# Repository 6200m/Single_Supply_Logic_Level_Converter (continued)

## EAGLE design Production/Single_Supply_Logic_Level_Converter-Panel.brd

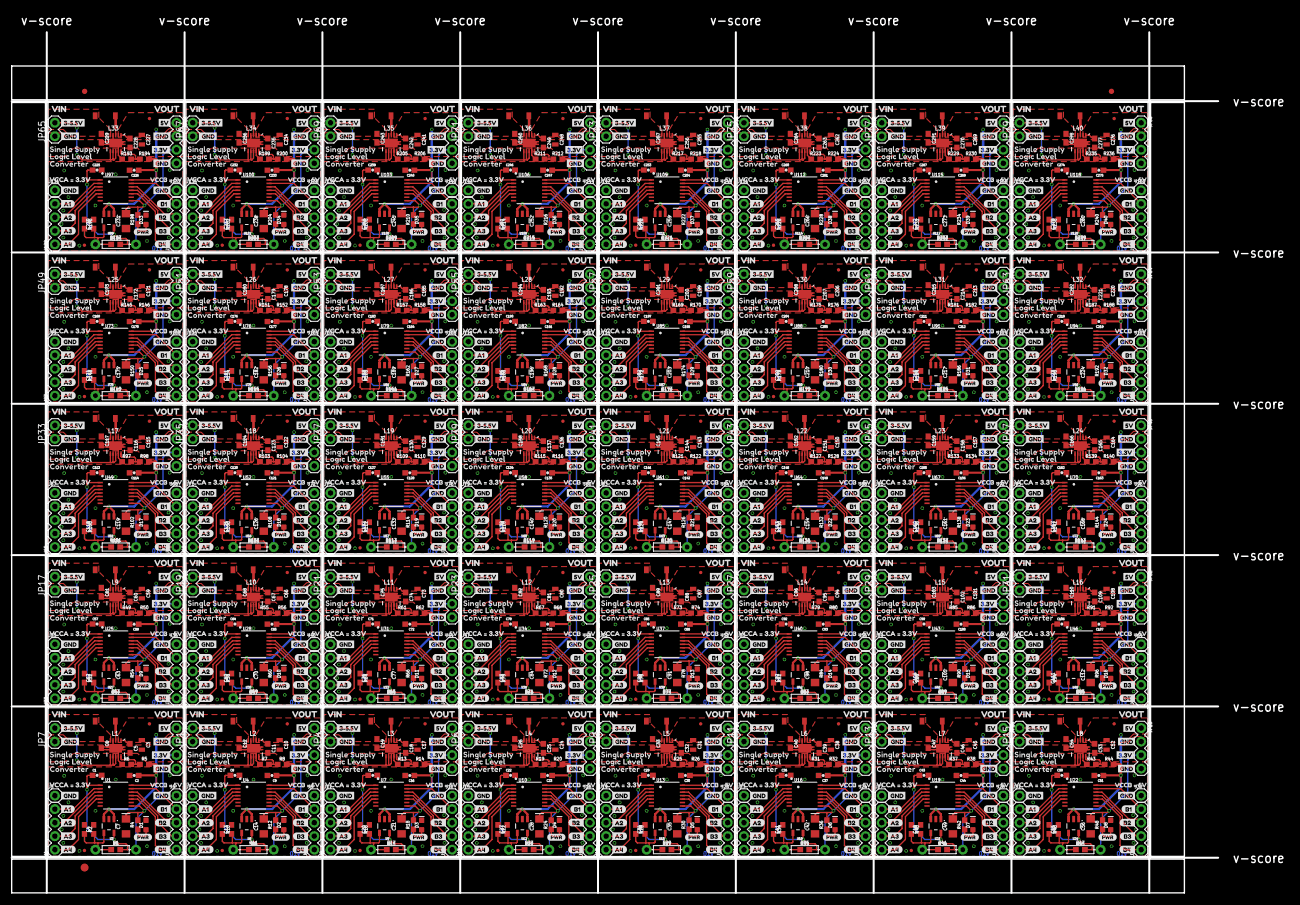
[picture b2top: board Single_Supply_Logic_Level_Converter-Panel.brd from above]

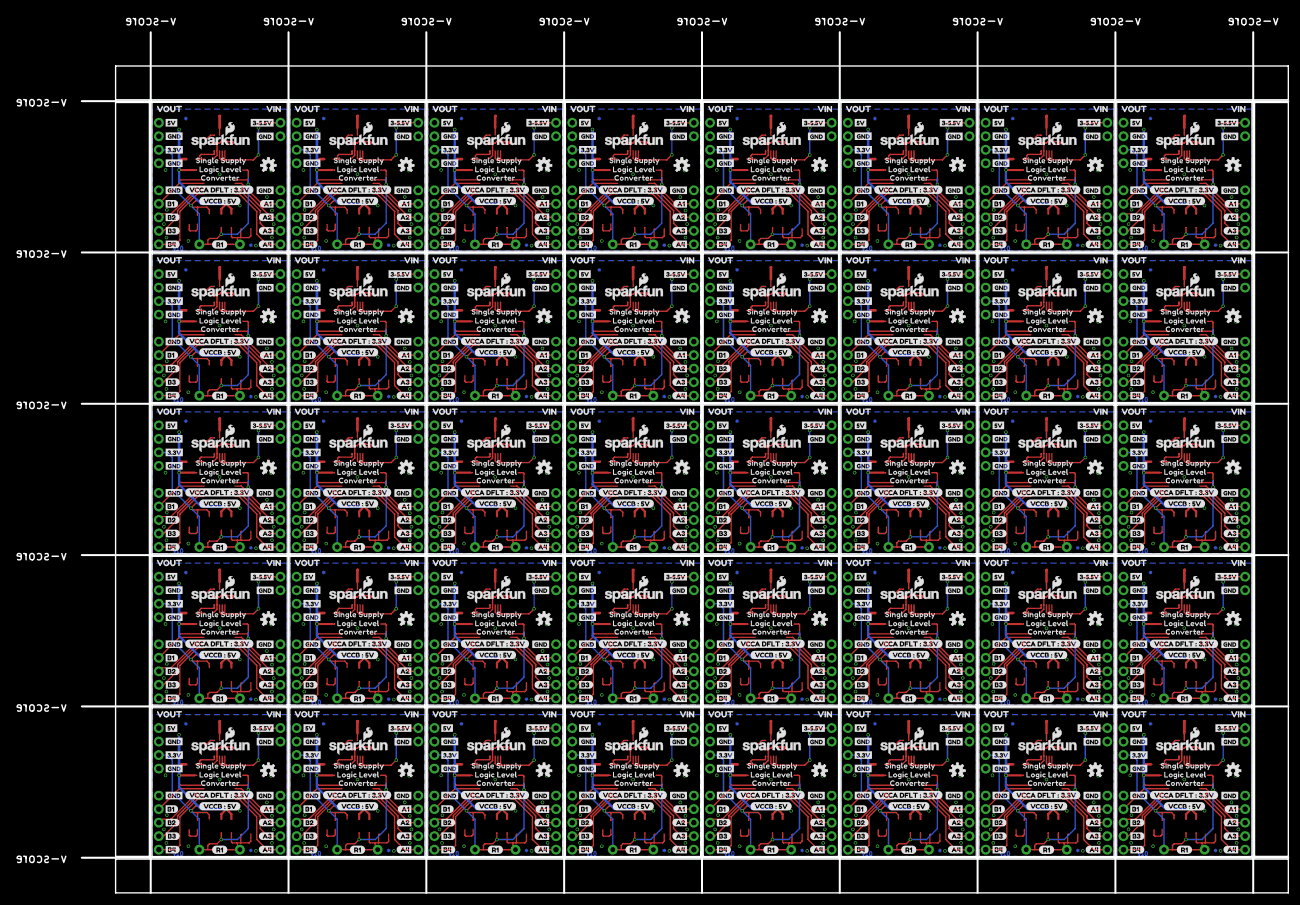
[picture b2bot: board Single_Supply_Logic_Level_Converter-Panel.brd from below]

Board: 2 copper layers, 226.8 x 161.8 mm, 3123 parts (1120 on the bottom side), 680 nets.

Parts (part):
C1, C2, C8, C9, C15, C16, C22, C23, C29, C30, C36, C37, C43, C44, C50, C51, C57, C58, C64, C65, C71, C72, C78, C79, C85, C86, C92, C93, C99, C100, C106, C107, C113, C114, C120, C121, C127, C128, C134, C135, C141, C142, C148, C149, C155, C156, C162, C163, C169, C170, C176, C177, C183, C184, C190, C191, C197, C198, C204, C205, C211, C212, C218, C219, C225, C226, C232, C233, C239, C240, C246, C247, C253, C254, C260, C261, C267, C268, C274, C275: 0.1uF; 0603-CAP
C3, C10, C17, C24, C31, C38, C45, C52, C59, C66, C73, C80, C87, C94, C101, C108, C115, C122, C129, C136, C143, C150, C157, C164, C171, C178, C185, C192, C199, C206, C213, C220, C227, C234, C241, C248, C255, C262, C269, C276: 22uF; 0805
C4, C13, C20, C27, C34, C41, C48, C55, C62, C69, C76, C83, C90, C97, C104, C111, C118, C125, C132, C139, C146, C153, C160, C167, C174, C181, C188, C195, C202, C209, C216, C223, C230, C237, C244, C251, C258, C265, C272, C279: 470pF; 0603
C5, C11, C18, C25, C32, C39, C46, C53, C60, C67, C74, C81, C88, C95, C102, C109, C116, C123, C130, C137, C144, C151, C158, C165, C172, C179, C186, C193, C200, C207, C214, C221, C228, C235, C242, C249, C256, C263, C270, C277: 0.1uF; 0603
C6, C12, C19, C26, C33, C40, C47, C54, C61, C68, C75, C82, C89, C96, C103, C110, C117, C124, C131, C138, C145, C152, C159, C166, C173, C180, C187, C194, C201, C208, C215, C222, C229, C236, C243, C250, C257, C264, C271, C278: 10uF; 0603
C7, C14, C21, C28, C35, C42, C49, C56, C63, C70, C77, C84, C91, C98, C105, C112, C119, C126, C133, C140, C147, C154, C161, C168, C175, C182, C189, C196, C203, C210, C217, C224, C231, C238, C245, C252, C259, C266, C273, C280: 10uF; EIA3216
D1, D2, D3, D4, D5, D6, D7, D8, D9, D10, D11, D12, D13, D14, D15, D16, D17, D18, D19, D20, D21, D22, D23, D24, D25, D26, D27, D28, D29, D30, D31, D32, D33, D34, D35, D36, D37, D38, D39, D40: RED; LED-0603
E$1, E$2: FIDUCIAL-1X2
E$3: FIDUCIAL-1.5X3
FD1, FD2, FD3, FD4, FD5, FD6, FD7, FD8, FD9, FD10, FD11, FD12, FD13, FD14, FD15, FD16, FD17, FD18, FD19, FD20, FD21, FD22, FD23, FD24, FD25, FD26, FD27, FD28, FD29, FD30, FD31, FD32, FD33, FD34, FD35, FD36, FD37, FD38, FD39, FD40, FD41, FD42, FD43, FD44, FD45, FD46, FD47, FD48, FD49, FD50, FD51, FD52, FD53, FD54, FD55, FD56, FD57, FD58, FD59, FD60, FD61, FD62, FD63, FD64, FD65, FD66, FD67, FD68, FD69, FD70, FD71, FD72, FD73, FD74, FD75, FD76, FD77, FD78, FD79, FD80, FD81, FD82, FD83, FD84, FD85, FD86, FD87, FD88, FD89, FD90, FD91, FD92, FD93, FD94, FD95, FD96, FD97, FD98, FD99, FD100, FD101, FD102, FD103, FD104, FD105, FD106, FD107, FD108, FD109, FD110, FD111, FD112, FD113, FD114, FD115, FD116, FD117, FD118, FD119, FD120, FD121, FD122, FD123, FD124, FD125, FD126, FD127, FD128, FD129, FD130, FD131, FD132, FD133, FD134, FD135, FD136, FD137, FD138, FD139, FD140, FD141, FD142, FD143, FD144, FD145, FD146, FD147, FD148, FD149, FD150, FD151, FD152, FD153, FD154, FD155, FD156, FD157, FD158, FD159, FD160: FIDUCIALUFIDUCIAL; FIDUCIAL-MICRO
J1, J2, J5, J6, J9, J10, J13, J14, J17, J18, J21, J22, J25, J26, J29, J30, J33, J34, J37, J38, J41, J42, J45, J46, J49, J50, J53, J54, J57, J58, J61, J62, J65, J66, J69, J70, J73, J74, J77, J78, J81, J82, J85, J86, J89, J90, J93, J94, J97, J98, J101, J102, J105, J106, J109, J110, J113, J114, J117, J118, J121, J122, J125, J126, J129, J130, J133, J134, J137, J138, J141, J142, J145, J146, J149, J150, J153, J154, J157, J158: 1X04
J3, J4, J7, J8, J11, J12, J15, J16, J19, J20, J23, J24, J27, J28, J31, J32, J35, J36, J39, J40, J43, J44, J47, J48, J51, J52, J55, J56, J59, J60, J63, J64, J67, J68, J71, J72, J75, J76, J79, J80, J83, J84, J87, J88, J91, J92, J95, J96, J99, J100, J103, J104, J107, J108, J111, J112, J115, J116, J119, J120, J123, J124, J127, J128, J131, J132, J135, J136, J139, J140, J143, J144, J147, J148, J151, J152, J155, J156, J159, J160: 1X01
JP1, JP4, JP6, JP7, JP9, JP11, JP13, JP15, JP17, JP19, JP21, JP23, JP25, JP27, JP29, JP31, JP33, JP35, JP37, JP39, JP41, JP43, JP45, JP47, JP49, JP51, JP53, JP55, JP57, JP59, JP61, JP63, JP65, JP67, JP69, JP71, JP73, JP75, JP77, JP79: VIN; 1X02
JP2, JP3, JP5, JP8, JP10, JP12, JP14, JP16, JP18, JP20, JP22, JP24, JP26, JP28, JP30, JP32, JP34, JP36, JP38, JP40, JP42, JP44, JP46, JP48, JP50, JP52, JP54, JP56, JP58, JP60, JP62, JP64, JP66, JP68, JP70, JP72, JP74, JP76, JP78, JP80: 455-1750-1-ND; 1X04
L1, L2, L3, L4, L5, L6, L7, L8, L9, L10, L11, L12, L13, L14, L15, L16, L17, L18, L19, L20, L21, L22, L23, L24, L25, L26, L27, L28, L29, L30, L31, L32, L33, L34, L35, L36, L37, L38, L39, L40: 2.2µH/±20%/1.5A; INDUCTOR_2.2UH
LOGO1, LOGO4, LOGO6, LOGO8, LOGO10, LOGO12, LOGO14, LOGO16, LOGO18, LOGO20, LOGO22, LOGO24, LOGO26, LOGO28, LOGO30, LOGO32, LOGO34, LOGO36, LOGO38, LOGO40, LOGO42, LOGO44, LOGO46, LOGO48, LOGO50, LOGO52, LOGO54, LOGO56, LOGO58, LOGO60, LOGO62, LOGO64, LOGO66, LOGO68, LOGO70, LOGO72, LOGO74, LOGO76, LOGO78, LOGO80: SFE_LOGO_NAME_FLAME.1_INCH; SFE_LOGO_NAME_FLAME_.1
LOGO2, LOGO3, LOGO5, LOGO7, LOGO9, LOGO11, LOGO13, LOGO15, LOGO17, LOGO19, LOGO21, LOGO23, LOGO25, LOGO27, LOGO29, LOGO31, LOGO33, LOGO35, LOGO37, LOGO39, LOGO41, LOGO43, LOGO45, LOGO47, LOGO49, LOGO51, LOGO53, LOGO55, LOGO57, LOGO59, LOGO61, LOGO63, LOGO65, LOGO67, LOGO69, LOGO71, LOGO73, LOGO75, LOGO77, LOGO79: OSHW-LOGOS; OSHW-LOGO-S
R1, R11, R17, R23, R29, R35, R41, R47, R53, R59, R65, R71, R77, R83, R89, R95, R101, R107, R113, R119, R125, R131, R137, R143, R149, R155, R161, R167, R173, R179, R185, R191, R197, R203, R209, R215, R221, R227, R233, R239: AXIAL-0.3
R2, R10, R16, R22, R28, R34, R40, R46, R52, R58, R64, R70, R76, R82, R88, R94, R100, R106, R112, R118, R124, R130, R136, R142, R148, R154, R160, R166, R172, R178, R184, R190, R196, R202, R208, R214, R220, R226, R232, R238: 22k; 0603
R3, R9, R15, R21, R27, R33, R39, R45, R51, R57, R63, R69, R75, R81, R87, R93, R99, R105, R111, R117, R123, R129, R135, R141, R147, R153, R159, R165, R171, R177, R183, R189, R195, R201, R207, R213, R219, R225, R231, R237: 13k; 0603
R4, R12, R18, R24, R30, R36, R42, R48, R54, R60, R66, R72, R78, R84, R90, R96, R102, R108, R114, R120, R126, R132, R138, R144, R150, R156, R162, R168, R174, R180, R186, R192, R198, R204, R210, R216, R222, R228, R234, R240: 1k; 0603
R5, R8, R14, R20, R26, R32, R38, R44, R50, R56, R62, R68, R74, R80, R86, R92, R98, R104, R110, R116, R122, R128, R134, R140, R146, R152, R158, R164, R170, R176, R182, R188, R194, R200, R206, R212, R218, R224, R230, R236: 1.8M; 0603
R6, R7, R13, R19, R25, R31, R37, R43, R49, R55, R61, R67, R73, R79, R85, R91, R97, R103, R109, R115, R121, R127, R133, R139, R145, R151, R157, R163, R169, R175, R181, R187, R193, R199, R205, R211, R217, R223, R229, R235: 200k; 0603
U1, U4, U7, U10, U13, U16, U19, U22, U25, U28, U31, U34, U37, U40, U43, U46, U49, U52, U55, U58, U61, U64, U67, U70, U73, U76, U79, U82, U85, U88, U91, U94, U97, U100, U103, U106, U109, U112, U115, U118: TXB0104; TSSOP14
U2, U5, U8, U11, U14, U17, U20, U23, U26, U29, U32, U35, U38, U41, U44, U47, U50, U53, U56, U59, U62, U65, U68, U71, U74, U77, U80, U83, U86, U89, U92, U95, U98, U101, U104, U107, U110, U113, U116, U119: TPS61200; QFN-10_PAD
U3, U6, U9, U12, U15, U18, U21, U24, U27, U30, U33, U36, U39, U42, U45, U48, U51, U54, U57, U60, U63, U66, U69, U72, U75, U78, U81, U84, U87, U90, U93, U96, U99, U102, U105, U108, U111, U114, U117, U120: MIC5205(ADJ); SOT23-5
U$1, U$29, U$97, U$145, U$193, U$241, U$289, U$337, U$385, U$433, U$481, U$529, U$577, U$625, U$673, U$721, U$769, U$817, U$865, U$913, U$961, U$1009, U$1057, U$1105, U$1153, U$1201, U$1249, U$1297, U$1345, U$1393, U$1441, U$1489, U$1537, U$1585, U$1633, U$1681, U$1729, U$1777, U$1825, U$1873: PWR0
U$2, U$5, U$10, U$43, U$98, U$101, U$146, U$149, U$194, U$197, U$242, U$245, U$290, U$293, U$338, U$341, U$386, U$389, U$434, U$437, U$482, U$485, U$530, U$533, U$578, U$581, U$626, U$629, U$674, U$677, U$722, U$725, U$770, U$773, U$818, U$821, U$866, U$869, U$914, U$917, U$962, U$965, U$1010, U$1013, U$1058, U$1061, U$1106, U$1109, U$1154, U$1157, U$1202, U$1205, U$1250, U$1253, U$1298, U$1301, U$1346, U$1349, U$1394, U$1397, U$1442, U$1445, U$1490, U$1493, U$1538, U$1541, U$1586, U$1589, U$1634, U$1637, U$1682, U$1685, U$1730, U$1733, U$1778, U$1781, U$1826, U$1829, U$1874, U$1877: CONVERTER0
U$3, U$6, U$11, U$45, U$99, U$102, U$147, U$150, U$195, U$198, U$243, U$246, U$291, U$294, U$339, U$342, U$387, U$390, U$435, U$438, U$483, U$486, U$531, U$534, U$579, U$582, U$627, U$630, U$675, U$678, U$723, U$726, U$771, U$774, U$819, U$822, U$867, U$870, U$915, U$918, U$963, U$966, U$1011, U$1014, U$1059, U$1062, U$1107, U$1110, U$1155, U$1158, U$1203, U$1206, U$1251, U$1254, U$1299, U$1302, U$1347, U$1350, U$1395, U$1398, U$1443, U$1446, U$1491, U$1494, U$1539, U$1542, U$1587, U$1590, U$1635, U$1638, U$1683, U$1686, U$1731, U$1734, U$1779, U$1782, U$1827, U$1830, U$1875, U$1878: LOGIC_LEVEL2
U$4, U$12, U$37, U$46, U$100, U$103, U$148, U$151, U$196, U$199, U$244, U$247, U$292, U$295, U$340, U$343, U$388, U$391, U$436, U$439, U$484, U$487, U$532, U$535, U$580, U$583, U$628, U$631, U$676, U$679, U$724, U$727, U$772, U$775, U$820, U$823, U$868, U$871, U$916, U$919, U$964, U$967, U$1012, U$1015, U$1060, U$1063, U$1108, U$1111, U$1156, U$1159, U$1204, U$1207, U$1252, U$1255, U$1300, U$1303, U$1348, U$1351, U$1396, U$1399, U$1444, U$1447, U$1492, U$1495, U$1540, U$1543, U$1588, U$1591, U$1636, U$1639, U$1684, U$1687, U$1732, U$1735, U$1780, U$1783, U$1828, U$1831, U$1876, U$1879: SINGLE_SUPPLY1
U$7, U$24, U$31, U$34, U$35, U$40, U$41, U$52, U$54, U$55, U$57, U$58, U$68, U$70, U$71, U$73, U$74, U$76, U$78, U$79, U$105, U$106, U$116, U$118, U$119, U$121, U$122, U$124, U$126, U$127, U$153, U$154, U$164, U$166, U$167, U$169, U$170, U$172, U$174, U$175, U$201, U$202, U$212, U$214, U$215, U$217, U$218, U$220, U$222, U$223, U$249, U$250, U$260, U$262, U$263, U$265, U$266, U$268, U$270, U$271, U$297, U$298, U$308, U$310, U$311, U$313, U$314, U$316, U$318, U$319, U$345, U$346, U$356, U$358, U$359, U$361, U$362, U$364, U$366, U$367, U$393, U$394, U$404, U$406, U$407, U$409, U$410, U$412, U$414, U$415, U$441, U$442, U$452, U$454, U$455, U$457, U$458, U$460, U$462, U$463, U$489, U$490, U$500, U$502, U$503, U$505, U$506, U$508, U$510, U$511, U$537, U$538, U$548, U$550, U$551, U$553, U$554, U$556, U$558, U$559, U$585, U$586, U$596, U$598, U$599, U$601, U$602, U$604, U$606, U$607, U$633, U$634, U$644, U$646, U$647, U$649, U$650, U$652, U$654, U$655, U$681, U$682, U$692, U$694, U$695, U$697, U$698, U$700, U$702, U$703, U$729, U$730, U$740, U$742, U$743, U$745, U$746, U$748, U$750, U$751, U$777, U$778, U$788, U$790, U$791, U$793, U$794, U$796, U$798, U$799, U$825, U$826, U$836, U$838, U$839, U$841, U$842, U$844, U$846, U$847, U$873, U$874, U$884, U$886, U$887, U$889, U$890, U$892, U$894, U$895, U$921, U$922, U$932, U$934, U$935, U$937, U$938, U$940, U$942, U$943, U$969, U$970, U$980, U$982, U$983, U$985, U$986, U$988, U$990, U$991, U$1017, U$1018, U$1028, U$1030, U$1031, U$1033, U$1034, U$1036, U$1038, U$1039, U$1065, U$1066, U$1076, U$1078, U$1079, U$1081, U$1082, U$1084, U$1086, U$1087, U$1113, U$1114, U$1124, U$1126, U$1127, U$1129, U$1130, U$1132, U$1134, U$1135, U$1161, U$1162, U$1172, U$1174, U$1175, U$1177, U$1178, U$1180, U$1182, U$1183, U$1209, U$1210, U$1220, U$1222, U$1223, U$1225, U$1226, U$1228, U$1230, U$1231, U$1257, U$1258, U$1268, U$1270, U$1271, U$1273, U$1274, U$1276, U$1278, U$1279, U$1305, U$1306, U$1316, U$1318, U$1319, U$1321, U$1322, U$1324, U$1326, U$1327, U$1353, U$1354, U$1364, U$1366, U$1367, U$1369, U$1370, U$1372, U$1374, U$1375, U$1401, U$1402, U$1412, U$1414, U$1415, U$1417, U$1418, U$1420, U$1422, U$1423, U$1449, U$1450, U$1460, U$1462, U$1463, U$1465, U$1466, U$1468, U$1470, U$1471, U$1497, U$1498, U$1508, U$1510, U$1511, U$1513, U$1514, U$1516, U$1518, U$1519, U$1545, U$1546, U$1556, U$1558, U$1559, U$1561, U$1562, U$1564, U$1566, U$1567, U$1593, U$1594, U$1604, U$1606, U$1607, U$1609, U$1610, U$1612, U$1614, U$1615, U$1641, U$1642, U$1652, U$1654, U$1655, U$1657, U$1658, U$1660, U$1662, U$1663, U$1689, U$1690, U$1700, U$1702, U$1703, U$1705, U$1706, U$1708, U$1710, U$1711, U$1737, U$1738, U$1748, U$1750, U$1751, U$1753, U$1754, U$1756, U$1758, U$1759, U$1785, U$1786, U$1796, U$1798, U$1799, U$1801, U$1802, U$1804, U$1806, U$1807, U$1833, U$1834, U$1844, U$1846, U$1847, U$1849, U$1850, U$1852, U$1854, U$1855, U$1881, U$1882, U$1892, U$1894, U$1895, U$1897, U$1898, U$1900, U$1902, U$1903: GND0
U$8, U$38, U$88, U$92, U$136, U$140, U$184, U$188, U$232, U$236, U$280, U$284, U$328, U$332, U$376, U$380, U$424, U$428, U$472, U$476, U$520, U$524, U$568, U$572, U$616, U$620, U$664, U$668, U$712, U$716, U$760, U$764, U$808, U$812, U$856, U$860, U$904, U$908, U$952, U$956, U$1000, U$1004, U$1048, U$1052, U$1096, U$1100, U$1144, U$1148, U$1192, U$1196, U$1240, U$1244, U$1288, U$1292, U$1336, U$1340, U$1384, U$1388, U$1432, U$1436, U$1480, U$1484, U$1528, U$1532, U$1576, U$1580, U$1624, U$1628, U$1672, U$1676, U$1720, U$1724, U$1768, U$1772, U$1816, U$1820, U$1864, U$1868, U$1912, U$1916: VIN1
U$9, U$80, U$128, U$176, U$224, U$272, U$320, U$368, U$416, U$464, U$512, U$560, U$608, U$656, U$704, U$752, U$800, U$848, U$896, U$944, U$992, U$1040, U$1088, U$1136, U$1184, U$1232, U$1280, U$1328, U$1376, U$1424, U$1472, U$1520, U$1568, U$1616, U$1664, U$1712, U$1760, U$1808, U$1856, U$1904: A10
U$13, U$63, U$111, U$159, U$207, U$255, U$303, U$351, U$399, U$447, U$495, U$543, U$591, U$639, U$687, U$735, U$783, U$831, U$879, U$927, U$975, U$1023, U$1071, U$1119, U$1167, U$1215, U$1263, U$1311, U$1359, U$1407, U$1455, U$1503, U$1551, U$1599, U$1647, U$1695, U$1743, U$1791, U$1839, U$1887: B1_12
U$14, U$81, U$129, U$177, U$225, U$273, U$321, U$369, U$417, U$465, U$513, U$561, U$609, U$657, U$705, U$753, U$801, U$849, U$897, U$945, U$993, U$1041, U$1089, U$1137, U$1185, U$1233, U$1281, U$1329, U$1377, U$1425, U$1473, U$1521, U$1569, U$1617, U$1665, U$1713, U$1761, U$1809, U$1857, U$1905: A21
U$15, U$82, U$130, U$178, U$226, U$274, U$322, U$370, U$418, U$466, U$514, U$562, U$610, U$658, U$706, U$754, U$802, U$850, U$898, U$946, U$994, U$1042, U$1090, U$1138, U$1186, U$1234, U$1282, U$1330, U$1378, U$1426, U$1474, U$1522, U$1570, U$1618, U$1666, U$1714, U$1762, U$1810, U$1858, U$1906: A32
U$16, U$83, U$131, U$179, U$227, U$275, U$323, U$371, U$419, U$467, U$515, U$563, U$611, U$659, U$707, U$755, U$803, U$851, U$899, U$947, U$995, U$1043, U$1091, U$1139, U$1187, U$1235, U$1283, U$1331, U$1379, U$1427, U$1475, U$1523, U$1571, U$1619, U$1667, U$1715, U$1763, U$1811, U$1859, U$1907: A43
U$17, U$84, U$132, U$180, U$228, U$276, U$324, U$372, U$420, U$468, U$516, U$564, U$612, U$660, U$708, U$756, U$804, U$852, U$900, U$948, U$996, U$1044, U$1092, U$1140, U$1188, U$1236, U$1284, U$1332, U$1380, U$1428, U$1476, U$1524, U$1572, U$1620, U$1668, U$1716, U$1764, U$1812, U$1860, U$1908: B14
U$18, U$85, U$133, U$181, U$229, U$277, U$325, U$373, U$421, U$469, U$517, U$565, U$613, U$661, U$709, U$757, U$805, U$853, U$901, U$949, U$997, U$1045, U$1093, U$1141, U$1189, U$1237, U$1285, U$1333, U$1381, U$1429, U$1477, U$1525, U$1573, U$1621, U$1669, U$1717, U$1765, U$1813, U$1861, U$1909: B25
U$19, U$64, U$112, U$160, U$208, U$256, U$304, U$352, U$400, U$448, U$496, U$544, U$592, U$640, U$688, U$736, U$784, U$832, U$880, U$928, U$976, U$1024, U$1072, U$1120, U$1168, U$1216, U$1264, U$1312, U$1360, U$1408, U$1456, U$1504, U$1552, U$1600, U$1648, U$1696, U$1744, U$1792, U$1840, U$1888: B2_11
U$20, U$65, U$113, U$161, U$209, U$257, U$305, U$353, U$401, U$449, U$497, U$545, U$593, U$641, U$689, U$737, U$785, U$833, U$881, U$929, U$977, U$1025, U$1073, U$1121, U$1169, U$1217, U$1265, U$1313, U$1361, U$1409, U$1457, U$1505, U$1553, U$1601, U$1649, U$1697, U$1745, U$1793, U$1841, U$1889: B3_10
U$21, U$39, U$50, U$72, U$104, U$120, U$152, U$168, U$200, U$216, U$248, U$264, U$296, U$312, U$344, U$360, U$392, U$408, U$440, U$456, U$488, U$504, U$536, U$552, U$584, U$600, U$632, U$648, U$680, U$696, U$728, U$744, U$776, U$792, U$824, U$840, U$872, U$888, U$920, U$936, U$968, U$984, U$1016, U$1032, U$1064, U$1080, U$1112, U$1128, U$1160, U$1176, U$1208, U$1224, U$1256, U$1272, U$1304, U$1320, U$1352, U$1368, U$1400, U$1416, U$1448, U$1464, U$1496, U$1512, U$1544, U$1560, U$1592, U$1608, U$1640, U$1656, U$1688, U$1704, U$1736, U$1752, U$1784, U$1800, U$1832, U$1848, U$1880, U$1896: 3#5#5V3
U$22, U$66, U$114, U$162, U$210, U$258, U$306, U$354, U$402, U$450, U$498, U$546, U$594, U$642, U$690, U$738, U$786, U$834, U$882, U$930, U$978, U$1026, U$1074, U$1122, U$1170, U$1218, U$1266, U$1314, U$1362, U$1410, U$1458, U$1506, U$1554, U$1602, U$1650, U$1698, U$1746, U$1794, U$1842, U$1890: B4_9
U$23, U$53, U$67, U$77, U$115, U$125, U$163, U$173, U$211, U$221, U$259, U$269, U$307, U$317, U$355, U$365, U$403, U$413, U$451, U$461, U$499, U$509, U$547, U$557, U$595, U$605, U$643, U$653, U$691, U$701, U$739, U$749, U$787, U$797, U$835, U$845, U$883, U$893, U$931, U$941, U$979, U$989, U$1027, U$1037, U$1075, U$1085, U$1123, U$1133, U$1171, U$1181, U$1219, U$1229, U$1267, U$1277, U$1315, U$1325, U$1363, U$1373, U$1411, U$1421, U$1459, U$1469, U$1507, U$1517, U$1555, U$1565, U$1603, U$1613, U$1651, U$1661, U$1699, U$1709, U$1747, U$1757, U$1795, U$1805, U$1843, U$1853, U$1891, U$1901: 3#3V2
U$25, U$59, U$107, U$155, U$203, U$251, U$299, U$347, U$395, U$443, U$491, U$539, U$587, U$635, U$683, U$731, U$779, U$827, U$875, U$923, U$971, U$1019, U$1067, U$1115, U$1163, U$1211, U$1259, U$1307, U$1355, U$1403, U$1451, U$1499, U$1547, U$1595, U$1643, U$1691, U$1739, U$1787, U$1835, U$1883: A14
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
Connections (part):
5V: C2.1, C3.1, JP3.1, R5.2, U1.14, U2.2, U3.1, U3.3
5V1: C9.1, C10.1, JP2.1, R8.2, U4.14, U5.2, U6.1, U6.3
5V2: C16.1, C17.1, JP5.1, R14.2, U7.14, U8.2, U9.1, U9.3
5V3: C23.1, C24.1, JP8.1, R20.2, U10.14, U11.2, U12.1, U12.3
5V4: C30.1, C31.1, JP10.1, R26.2, U13.14, U14.2, U15.1, U15.3
5V5: C37.1, C38.1, JP12.1, R32.2, U16.14, U17.2, U18.1, U18.3
5V6: C44.1, C45.1, JP14.1, R38.2, U19.14, U20.2, U21.1, U21.3
5V7: C51.1, C52.1, JP16.1, R44.2, U22.14, U23.2, U24.1, U24.3
5V8: C58.1, C59.1, JP18.1, R50.2, U25.14, U26.2, U27.1, U27.3
5V9: C65.1, C66.1, JP20.1, R56.2, U28.14, U29.2, U30.1, U30.3
5V10: C72.1, C73.1, JP22.1, R62.2, U31.14, U32.2, U33.1, U33.3
5V11: C79.1, C80.1, JP24.1, R68.2, U34.14, U35.2, U36.1, U36.3
5V12: C86.1, C87.1, JP26.1, R74.2, U37.14, U38.2, U39.1, U39.3
5V13: C93.1, C94.1, JP28.1, R80.2, U40.14, U41.2, U42.1, U42.3
5V14: C100.1, C101.1, JP30.1, R86.2, U43.14, U44.2, U45.1, U45.3
5V15: C107.1, C108.1, JP32.1, R92.2, U46.14, U47.2, U48.1, U48.3
5V16: C114.1, C115.1, JP34.1, R98.2, U49.14, U50.2, U51.1, U51.3
5V17: C121.1, C122.1, JP36.1, R104.2, U52.14, U53.2, U54.1, U54.3
5V18: C128.1, C129.1, JP38.1, R110.2, U55.14, U56.2, U57.1, U57.3
5V19: C135.1, C136.1, JP40.1, R116.2, U58.14, U59.2, U60.1, U60.3
5V20: C142.1, C143.1, JP42.1, R122.2, U61.14, U62.2, U63.1, U63.3
5V21: C149.1, C150.1, JP44.1, R128.2, U64.14, U65.2, U66.1, U66.3
5V22: C156.1, C157.1, JP46.1, R134.2, U67.14, U68.2, U69.1, U69.3
5V23: C163.1, C164.1, JP48.1, R140.2, U70.14, U71.2, U72.1, U72.3
5V24: C170.1, C171.1, JP50.1, R146.2, U73.14, U74.2, U75.1, U75.3
5V25: C177.1, C178.1, JP52.1, R152.2, U76.14, U77.2, U78.1, U78.3
5V26: C184.1, C185.1, JP54.1, R158.2, U79.14, U80.2, U81.1, U81.3
5V27: C191.1, C192.1, JP56.1, R164.2, U82.14, U83.2, U84.1, U84.3
5V28: C198.1, C199.1, JP58.1, R170.2, U85.14, U86.2, U87.1, U87.3
5V29: C205.1, C206.1, JP60.1, R176.2, U88.14, U89.2, U90.1, U90.3
5V30: C212.1, C213.1, JP62.1, R182.2, U91.14, U92.2, U93.1, U93.3
5V31: C219.1, C220.1, JP64.1, R188.2, U94.14, U95.2, U96.1, U96.3
5V32: C226.1, C227.1, JP66.1, R194.2, U97.14, U98.2, U99.1, U99.3
5V33: C233.1, C234.1, JP68.1, R200.2, U100.14, U101.2, U102.1, U102.3
5V34: C240.1, C241.1, JP70.1, R206.2, U103.14, U104.2, U105.1, U105.3
5V35: C247.1, C248.1, JP72.1, R212.2, U106.14, U107.2, U108.1, U108.3
5V36: C254.1, C255.1, JP74.1, R218.2, U109.14, U110.2, U111.1, U111.3
5V37: C261.1, C262.1, JP76.1, R224.2, U112.14, U113.2, U114.1, U114.3
5V38: C268.1, C269.1, JP78.1, R230.2, U115.14, U116.2, U117.1, U117.3
5V39: C275.1, C276.1, JP80.1, R236.2, U118.14, U119.2, U120.1, U120.3
A1: J1.4, U1.2
A2: J1.3, U1.3
A3: J1.2, U1.4
A4: J1.1, U1.5
A5: J5.3, U4.3
A6: J5.1, U4.5
A7: J5.2, U4.4
A8: J5.4, U4.2
A9: J9.3, U7.3
A10: J9.1, U7.5
A11: J9.2, U7.4
A12: J9.4, U7.2
A13: J13.3, U10.3
A14: J13.1, U10.5
A15: J13.2, U10.4
A16: J13.4, U10.2
A17: J17.3, U13.3
A18: J17.1, U13.5
A19: J17.2, U13.4
A20: J17.4, U13.2
A21: J21.3, U16.3
A22: J21.1, U16.5
A23: J21.2, U16.4
A24: J21.4, U16.2
A25: J25.3, U19.3
A26: J25.1, U19.5
A27: J25.2, U19.4
A28: J25.4, U19.2
A29: J29.3, U22.3
A30: J29.1, U22.5
A31: J29.2, U22.4
A32: J29.4, U22.2
A33: J33.3, U25.3
A34: J33.1, U25.5
A35: J33.2, U25.4
A36: J33.4, U25.2
A37: J37.3, U28.3
A38: J37.1, U28.5
A39: J37.2, U28.4
A40: J37.4, U28.2
A41: J41.3, U31.3
A42: J41.1, U31.5
A43: J41.2, U31.4
A44: J41.4, U31.2
A45: J45.3, U34.3
A46: J45.1, U34.5
A47: J45.2, U34.4
A48: J45.4, U34.2
A49: J49.3, U37.3
A50: J49.1, U37.5
A51: J49.2, U37.4
A52: J49.4, U37.2
A53: J53.3, U40.3
A54: J53.1, U40.5
A55: J53.2, U40.4
A56: J53.4, U40.2
A57: J57.3, U43.3
A58: J57.1, U43.5
A59: J57.2, U43.4
A60: J57.4, U43.2
A61: J61.3, U46.3
A62: J61.1, U46.5
A63: J61.2, U46.4
A64: J61.4, U46.2
A65: J65.3, U49.3
A66: J65.1, U49.5
A67: J65.2, U49.4
A68: J65.4, U49.2
A69: J69.3, U52.3
A70: J69.1, U52.5
A71: J69.2, U52.4
A72: J69.4, U52.2
A73: J73.3, U55.3
A74: J73.1, U55.5
A75: J73.2, U55.4
A76: J73.4, U55.2
A77: J77.3, U58.3
A78: J77.1, U58.5
A79: J77.2, U58.4
A80: J77.4, U58.2
A81: J81.3, U61.3
A82: J81.1, U61.5
A83: J81.2, U61.4
A84: J81.4, U61.2
A85: J85.3, U64.3
A86: J85.1, U64.5
A87: J85.2, U64.4
A88: J85.4, U64.2
A89: J89.3, U67.3
A90: J89.1, U67.5
A91: J89.2, U67.4
A92: J89.4, U67.2
A93: J93.3, U70.3
A94: J93.1, U70.5
A95: J93.2, U70.4
A96: J93.4, U70.2
A97: J97.3, U73.3
A98: J97.1, U73.5
A99: J97.2, U73.4
A100: J97.4, U73.2
A101: J101.3, U76.3
A102: J101.1, U76.5
A103: J101.2, U76.4
A104: J101.4, U76.2
A105: J105.3, U79.3
A106: J105.1, U79.5
A107: J105.2, U79.4
A108: J105.4, U79.2
A109: J109.3, U82.3
A110: J109.1, U82.5
A111: J109.2, U82.4
A112: J109.4, U82.2
A113: J113.3, U85.3
A114: J113.1, U85.5
A115: J113.2, U85.4
A116: J113.4, U85.2
A117: J117.3, U88.3
A118: J117.1, U88.5
A119: J117.2, U88.4
A120: J117.4, U88.2
A121: J121.3, U91.3
A122: J121.1, U91.5
A123: J121.2, U91.4
A124: J121.4, U91.2
A125: J125.3, U94.3
A126: J125.1, U94.5
A127: J125.2, U94.4
A128: J125.4, U94.2
A129: J129.3, U97.3
A130: J129.1, U97.5
A131: J129.2, U97.4
A132: J129.4, U97.2
A133: J133.3, U100.3
A134: J133.1, U100.5
A135: J133.2, U100.4
A136: J133.4, U100.2
A137: J137.3, U103.3
A138: J137.1, U103.5
A139: J137.2, U103.4
A140: J137.4, U103.2
A141: J141.3, U106.3
A142: J141.1, U106.5
A143: J141.2, U106.4
A144: J141.4, U106.2
A145: J145.3, U109.3
A146: J145.1, U109.5
A147: J145.2, U109.4
A148: J145.4, U109.2
A149: J149.3, U112.3
A150: J149.1, U112.5
A151: J149.2, U112.4
A152: J149.4, U112.2
A153: J153.3, U115.3
A154: J153.1, U115.5
A155: J153.2, U115.4
A156: J153.4, U115.2
A157: J157.3, U118.3
A158: J157.1, U118.5
A159: J157.2, U118.4
A160: J157.4, U118.2
B1: J2.4, U1.13
B2: J2.3, U1.12
B3: J2.2, U1.11
B4: J2.1, U1.10
B5: J6.4, U4.13
B6: J6.2, U4.11
B7: J6.1, U4.10
B8: J6.3, U4.12
B9: J10.4, U7.13
B10: J10.2, U7.11
B11: J10.1, U7.10
B12: J10.3, U7.12
B13: J14.4, U10.13
B14: J14.2, U10.11
B15: J14.1, U10.10
B16: J14.3, U10.12
B17: J18.4, U13.13
B18: J18.2, U13.11
B19: J18.1, U13.10
B20: J18.3, U13.12
B21: J22.4, U16.13
B22: J22.2, U16.11
B23: J22.1, U16.10
B24: J22.3, U16.12
B25: J26.4, U19.13
B26: J26.2, U19.11
B27: J26.1, U19.10
B28: J26.3, U19.12
B29: J30.4, U22.13
B30: J30.2, U22.11
B31: J30.1, U22.10
B32: J30.3, U22.12
B33: J34.4, U25.13
B34: J34.2, U25.11
B35: J34.1, U25.10
B36: J34.3, U25.12
B37: J38.4, U28.13
B38: J38.2, U28.11
B39: J38.1, U28.10
B40: J38.3, U28.12
B41: J42.4, U31.13
B42: J42.2, U31.11
B43: J42.1, U31.10
B44: J42.3, U31.12
B45: J46.4, U34.13
B46: J46.2, U34.11
B47: J46.1, U34.10
B48: J46.3, U34.12
B49: J50.4, U37.13
B50: J50.2, U37.11
B51: J50.1, U37.10
B52: J50.3, U37.12
B53: J54.4, U40.13
B54: J54.2, U40.11
B55: J54.1, U40.10
B56: J54.3, U40.12
B57: J58.4, U43.13
B58: J58.2, U43.11
B59: J58.1, U43.10
B60: J58.3, U43.12
B61: J62.4, U46.13
B62: J62.2, U46.11
B63: J62.1, U46.10
B64: J62.3, U46.12
B65: J66.4, U49.13
B66: J66.2, U49.11
B67: J66.1, U49.10
B68: J66.3, U49.12
B69: J70.4, U52.13
B70: J70.2, U52.11
B71: J70.1, U52.10
B72: J70.3, U52.12
B73: J74.4, U55.13
B74: J74.2, U55.11
B75: J74.1, U55.10
B76: J74.3, U55.12
B77: J78.4, U58.13
B78: J78.2, U58.11
B79: J78.1, U58.10
B80: J78.3, U58.12
B81: J82.4, U61.13
B82: J82.2, U61.11
B83: J82.1, U61.10
B84: J82.3, U61.12
B85: J86.4, U64.13
B86: J86.2, U64.11
B87: J86.1, U64.10
B88: J86.3, U64.12
B89: J90.4, U67.13
B90: J90.2, U67.11
B91: J90.1, U67.10
B92: J90.3, U67.12
B93: J94.4, U70.13
B94: J94.2, U70.11
B95: J94.1, U70.10
B96: J94.3, U70.12
B97: J98.4, U73.13
B98: J98.2, U73.11
B99: J98.1, U73.10
B100: J98.3, U73.12
B101: J102.4, U76.13
B102: J102.2, U76.11
B103: J102.1, U76.10
B104: J102.3, U76.12
B105: J106.4, U79.13
B106: J106.2, U79.11
B107: J106.1, U79.10
B108: J106.3, U79.12
B109: J110.4, U82.13
B110: J110.2, U82.11
B111: J110.1, U82.10
B112: J110.3, U82.12
B113: J114.4, U85.13
B114: J114.2, U85.11
B115: J114.1, U85.10
B116: J114.3, U85.12
B117: J118.4, U88.13
B118: J118.2, U88.11
B119: J118.1, U88.10
B120: J118.3, U88.12
B121: J122.4, U91.13
B122: J122.2, U91.11
B123: J122.1, U91.10
B124: J122.3, U91.12
B125: J126.4, U94.13
B126: J126.2, U94.11
B127: J126.1, U94.10
B128: J126.3, U94.12
B129: J130.4, U97.13
B130: J130.2, U97.11
B131: J130.1, U97.10
B132: J130.3, U97.12
B133: J134.4, U100.13
B134: J134.2, U100.11
B135: J134.1, U100.10
B136: J134.3, U100.12
B137: J138.4, U103.13
B138: J138.2, U103.11
B139: J138.1, U103.10
B140: J138.3, U103.12
B141: J142.4, U106.13
B142: J142.2, U106.11
B143: J142.1, U106.10
B144: J142.3, U106.12
B145: J146.4, U109.13
B146: J146.2, U109.11
B147: J146.1, U109.10
B148: J146.3, U109.12
B149: J150.4, U112.13
B150: J150.2, U112.11
B151: J150.1, U112.10
B152: J150.3, U112.12
B153: J154.4, U115.13
B154: J154.2, U115.11
B155: J154.1, U115.10
B156: J154.3, U115.12
B157: J158.4, U118.13
B158: J158.2, U118.11
B159: J158.1, U118.10
B160: J158.3, U118.12
FB: R5.1, R6.2, U2.10
FB1: R7.2, R8.1, U5.10
FB2: R13.2, R14.1, U8.10
FB3: R19.2, R20.1, U11.10
FB4: R25.2, R26.1, U14.10
FB5: R31.2, R32.1, U17.10
FB6: R37.2, R38.1, U20.10
FB7: R43.2, R44.1, U23.10
FB8: R49.2, R50.1, U26.10
FB9: R55.2, R56.1, U29.10
FB10: R61.2, R62.1, U32.10
FB11: R67.2, R68.1, U35.10
FB12: R73.2, R74.1, U38.10
FB13: R79.2, R80.1, U41.10
FB14: R85.2, R86.1, U44.10
FB15: R91.2, R92.1, U47.10
FB16: R97.2, R98.1, U50.10
FB17: R103.2, R104.1, U53.10
FB18: R109.2, R110.1, U56.10
FB19: R115.2, R116.1, U59.10
FB20: R121.2, R122.1, U62.10
FB21: R127.2, R128.1, U65.10
FB22: R133.2, R134.1, U68.10
FB23: R139.2, R140.1, U71.10
FB24: R145.2, R146.1, U74.10
FB25: R151.2, R152.1, U77.10
FB26: R157.2, R158.1, U80.10
FB27: R163.2, R164.1, U83.10
FB28: R169.2, R170.1, U86.10
FB29: R175.2, R176.1, U89.10
FB30: R181.2, R182.1, U92.10
FB31: R187.2, R188.1, U95.10
FB32: R193.2, R194.1, U98.10
FB33: R199.2, R200.1, U101.10
FB34: R205.2, R206.1, U104.10
FB35: R211.2, R212.1, U107.10
FB36: R217.2, R218.1, U110.10
FB37: R223.2, R224.1, U113.10
FB38: R229.2, R230.1, U116.10
FB39: R235.2, R236.1, U119.10
GND: C1.2, C2.2, C3.2, C4.2, C5.2, C6.2, C7.-, D1.C, J3.1, J4.1, JP3.2, JP3.4, JP7.1, R2.1, R6.1, U1.7, U2.4, U2.9, U2.11, U2.12, U2.13, U2.14, U2.15, U3.2
GND1: C8.2, C9.2, C10.2, C11.2, C12.2, C13.2, C14.-, D2.C, J7.1, J8.1, JP1.1, JP2.2, JP2.4, R7.1, R10.1, U4.7, U5.4, U5.9, U5.11, U5.12, U5.13, U5.14, U5.15, U6.2
GND2: C15.2, C16.2, C17.2, C18.2, C19.2, C20.2, C21.-, D3.C, J11.1, J12.1, JP4.1, JP5.2, JP5.4, R13.1, R16.1, U7.7, U8.4, U8.9, U8.11, U8.12, U8.13, U8.14, U8.15, U9.2
GND3: C22.2, C23.2, C24.2, C25.2, C26.2, C27.2, C28.-, D4.C, J15.1, J16.1, JP6.1, JP8.2, JP8.4, R19.1, R22.1, U10.7, U11.4, U11.9, U11.11, U11.12, U11.13, U11.14, U11.15, U12.2
GND4: C29.2, C30.2, C31.2, C32.2, C33.2, C34.2, C35.-, D5.C, J19.1, J20.1, JP9.1, JP10.2, JP10.4, R25.1, R28.1, U13.7, U14.4, U14.9, U14.11, U14.12, U14.13, U14.14, U14.15, U15.2
GND5: C36.2, C37.2, C38.2, C39.2, C40.2, C41.2, C42.-, D6.C, J23.1, J24.1, JP11.1, JP12.2, JP12.4, R31.1, R34.1, U16.7, U17.4, U17.9, U17.11, U17.12, U17.13, U17.14, U17.15, U18.2
GND6: C43.2, C44.2, C45.2, C46.2, C47.2, C48.2, C49.-, D7.C, J27.1, J28.1, JP13.1, JP14.2, JP14.4, R37.1, R40.1, U19.7, U20.4, U20.9, U20.11, U20.12, U20.13, U20.14, U20.15, U21.2
GND7: C50.2, C51.2, C52.2, C53.2, C54.2, C55.2, C56.-, D8.C, J31.1, J32.1, JP15.1, JP16.2, JP16.4, R43.1, R46.1, U22.7, U23.4, U23.9, U23.11, U23.12, U23.13, U23.14, U23.15, U24.2
GND8: C57.2, C58.2, C59.2, C60.2, C61.2, C62.2, C63.-, D9.C, J35.1, J36.1, JP17.1, JP18.2, JP18.4, R49.1, R52.1, U25.7, U26.4, U26.9, U26.11, U26.12, U26.13, U26.14, U26.15, U27.2
GND9: C64.2, C65.2, C66.2, C67.2, C68.2, C69.2, C70.-, D10.C, J39.1, J40.1, JP19.1, JP20.2, JP20.4, R55.1, R58.1, U28.7, U29.4, U29.9, U29.11, U29.12, U29.13, U29.14, U29.15, U30.2
GND10: C71.2, C72.2, C73.2, C74.2, C75.2, C76.2, C77.-, D11.C, J43.1, J44.1, JP21.1, JP22.2, JP22.4, R61.1, R64.1, U31.7, U32.4, U32.9, U32.11, U32.12, U32.13, U32.14, U32.15, U33.2
GND11: C78.2, C79.2, C80.2, C81.2, C82.2, C83.2, C84.-, D12.C, J47.1, J48.1, JP23.1, JP24.2, JP24.4, R67.1, R70.1, U34.7, U35.4, U35.9, U35.11, U35.12, U35.13, U35.14, U35.15, U36.2
GND12: C85.2, C86.2, C87.2, C88.2, C89.2, C90.2, C91.-, D13.C, J51.1, J52.1, JP25.1, JP26.2, JP26.4, R73.1, R76.1, U37.7, U38.4, U38.9, U38.11, U38.12, U38.13, U38.14, U38.15, U39.2
GND13: C92.2, C93.2, C94.2, C95.2, C96.2, C97.2, C98.-, D14.C, J55.1, J56.1, JP27.1, JP28.2, JP28.4, R79.1, R82.1, U40.7, U41.4, U41.9, U41.11, U41.12, U41.13, U41.14, U41.15, U42.2
GND14: C99.2, C100.2, C101.2, C102.2, C103.2, C104.2, C105.-, D15.C, J59.1, J60.1, JP29.1, JP30.2, JP30.4, R85.1, R88.1, U43.7, U44.4, U44.9, U44.11, U44.12, U44.13, U44.14, U44.15, U45.2
GND15: C106.2, C107.2, C108.2, C109.2, C110.2, C111.2, C112.-, D16.C, J63.1, J64.1, JP31.1, JP32.2, JP32.4, R91.1, R94.1, U46.7, U47.4, U47.9, U47.11, U47.12, U47.13, U47.14, U47.15, U48.2
GND16: C113.2, C114.2, C115.2, C116.2, C117.2, C118.2, C119.-, D17.C, J67.1, J68.1, JP33.1, JP34.2, JP34.4, R97.1, R100.1, U49.7, U50.4, U50.9, U50.11, U50.12, U50.13, U50.14, U50.15, U51.2
GND17: C120.2, C121.2, C122.2, C123.2, C124.2, C125.2, C126.-, D18.C, J71.1, J72.1, JP35.1, JP36.2, JP36.4, R103.1, R106.1, U52.7, U53.4, U53.9, U53.11, U53.12, U53.13, U53.14, U53.15, U54.2
GND18: C127.2, C128.2, C129.2, C130.2, C131.2, C132.2, C133.-, D19.C, J75.1, J76.1, JP37.1, JP38.2, JP38.4, R109.1, R112.1, U55.7, U56.4, U56.9, U56.11, U56.12, U56.13, U56.14, U56.15, U57.2
GND19: C134.2, C135.2, C136.2, C137.2, C138.2, C139.2, C140.-, D20.C, J79.1, J80.1, JP39.1, JP40.2, JP40.4, R115.1, R118.1, U58.7, U59.4, U59.9, U59.11, U59.12, U59.13, U59.14, U59.15, U60.2
GND20: C141.2, C142.2, C143.2, C144.2, C145.2, C146.2, C147.-, D21.C, J83.1, J84.1, JP41.1, JP42.2, JP42.4, R121.1, R124.1, U61.7, U62.4, U62.9, U62.11, U62.12, U62.13, U62.14, U62.15, U63.2
GND21: C148.2, C149.2, C150.2, C151.2, C152.2, C153.2, C154.-, D22.C, J87.1, J88.1, JP43.1, JP44.2, JP44.4, R127.1, R130.1, U64.7, U65.4, U65.9, U65.11, U65.12, U65.13, U65.14, U65.15, U66.2
GND22: C155.2, C156.2, C157.2, C158.2, C159.2, C160.2, C161.-, D23.C, J91.1, J92.1, JP45.1, JP46.2, JP46.4, R133.1, R136.1, U67.7, U68.4, U68.9, U68.11, U68.12, U68.13, U68.14, U68.15, U69.2
GND23: C162.2, C163.2, C164.2, C165.2, C166.2, C167.2, C168.-, D24.C, J95.1, J96.1, JP47.1, JP48.2, JP48.4, R139.1, R142.1, U70.7, U71.4, U71.9, U71.11, U71.12, U71.13, U71.14, U71.15, U72.2
GND24: C169.2, C170.2, C171.2, C172.2, C173.2, C174.2, C175.-, D25.C, J99.1, J100.1, JP49.1, JP50.2, JP50.4, R145.1, R148.1, U73.7, U74.4, U74.9, U74.11, U74.12, U74.13, U74.14, U74.15, U75.2
GND25: C176.2, C177.2, C178.2, C179.2, C180.2, C181.2, C182.-, D26.C, J103.1, J104.1, JP51.1, JP52.2, JP52.4, R151.1, R154.1, U76.7, U77.4, U77.9, U77.11, U77.12, U77.13, U77.14, U77.15, U78.2
GND26: C183.2, C184.2, C185.2, C186.2, C187.2, C188.2, C189.-, D27.C, J107.1, J108.1, JP53.1, JP54.2, JP54.4, R157.1, R160.1, U79.7, U80.4, U80.9, U80.11, U80.12, U80.13, U80.14, U80.15, U81.2
GND27: C190.2, C191.2, C192.2, C193.2, C194.2, C195.2, C196.-, D28.C, J111.1, J112.1, JP55.1, JP56.2, JP56.4, R163.1, R166.1, U82.7, U83.4, U83.9, U83.11, U83.12, U83.13, U83.14, U83.15, U84.2
GND28: C197.2, C198.2, C199.2, C200.2, C201.2, C202.2, C203.-, D29.C, J115.1, J116.1, JP57.1, JP58.2, JP58.4, R169.1, R172.1, U85.7, U86.4, U86.9, U86.11, U86.12, U86.13, U86.14, U86.15, U87.2
GND29: C204.2, C205.2, C206.2, C207.2, C208.2, C209.2, C210.-, D30.C, J119.1, J120.1, JP59.1, JP60.2, JP60.4, R175.1, R178.1, U88.7, U89.4, U89.9, U89.11, U89.12, U89.13, U89.14, U89.15, U90.2
GND30: C211.2, C212.2, C213.2, C214.2, C215.2, C216.2, C217.-, D31.C, J123.1, J124.1, JP61.1, JP62.2, JP62.4, R181.1, R184.1, U91.7, U92.4, U92.9, U92.11, U92.12, U92.13, U92.14, U92.15, U93.2
GND31: C218.2, C219.2, C220.2, C221.2, C222.2, C223.2, C224.-, D32.C, J127.1, J128.1, JP63.1, JP64.2, JP64.4, R187.1, R190.1, U94.7, U95.4, U95.9, U95.11, U95.12, U95.13, U95.14, U95.15, U96.2
GND32: C225.2, C226.2, C227.2, C228.2, C229.2, C230.2, C231.-, D33.C, J131.1, J132.1, JP65.1, JP66.2, JP66.4, R193.1, R196.1, U97.7, U98.4, U98.9, U98.11, U98.12, U98.13, U98.14, U98.15, U99.2
GND33: C232.2, C233.2, C234.2, C235.2, C236.2, C237.2, C238.-, D34.C, J135.1, J136.1, JP67.1, JP68.2, JP68.4, R199.1, R202.1, U100.7, U101.4, U101.9, U101.11, U101.12, U101.13, U101.14, U101.15, U102.2
GND34: C239.2, C240.2, C241.2, C242.2, C243.2, C244.2, C245.-, D35.C, J139.1, J140.1, JP69.1, JP70.2, JP70.4, R205.1, R208.1, U103.7, U104.4, U104.9, U104.11, U104.12, U104.13, U104.14, U104.15, U105.2
GND35: C246.2, C247.2, C248.2, C249.2, C250.2, C251.2, C252.-, D36.C, J143.1, J144.1, JP71.1, JP72.2, JP72.4, R211.1, R214.1, U106.7, U107.4, U107.9, U107.11, U107.12, U107.13, U107.14, U107.15, U108.2
GND36: C253.2, C254.2, C255.2, C256.2, C257.2, C258.2, C259.-, D37.C, J147.1, J148.1, JP73.1, JP74.2, JP74.4, R217.1, R220.1, U109.7, U110.4, U110.9, U110.11, U110.12, U110.13, U110.14, U110.15, U111.2
GND37: C260.2, C261.2, C262.2, C263.2, C264.2, C265.2, C266.-, D38.C, J151.1, J152.1, JP75.1, JP76.2, JP76.4, R223.1, R226.1, U112.7, U113.4, U113.9, U113.11, U113.12, U113.13, U113.14, U113.15, U114.2
GND38: C267.2, C268.2, C269.2, C270.2, C271.2, C272.2, C273.-, D39.C, J155.1, J156.1, JP77.1, JP78.2, JP78.4, R229.1, R232.1, U115.7, U116.4, U116.9, U116.11, U116.12, U116.13, U116.14, U116.15, U117.2
GND39: C274.2, C275.2, C276.2, C277.2, C278.2, C279.2, C280.-, D40.C, J159.1, J160.1, JP79.1, JP80.2, JP80.4, R235.1, R238.1, U118.7, U119.4, U119.9, U119.11, U119.12, U119.13, U119.14, U119.15, U120.2
unnamed: L2.P$1, U5.3
unnamed: C11.1, U5.1
unnamed: D1.A, R4.1
unnamed: C13.1, R9.1, R10.2, R11.P$1, U6.4
unnamed: L1.P$1, U2.3
unnamed: C5.1, U2.1
unnamed: D2.A, R12.1
unnamed: L3.P$1, U8.3
unnamed: C18.1, U8.1
unnamed: C20.1, R15.1, R16.2, R17.P$1, U9.4
unnamed: C4.1, R1.P$1, R2.2, R3.1, U3.4
unnamed: D3.A, R18.1
unnamed: L4.P$1, U11.3
unnamed: C25.1, U11.1
unnamed: C27.1, R21.1, R22.2, R23.P$1, U12.4
unnamed: D4.A, R24.1
unnamed: L5.P$1, U14.3
unnamed: C32.1, U14.1
unnamed: C34.1, R27.1, R28.2, R29.P$1, U15.4
unnamed: D5.A, R30.1
unnamed: L6.P$1, U17.3
unnamed: C39.1, U17.1
unnamed: C41.1, R33.1, R34.2, R35.P$1, U18.4
unnamed: D6.A, R36.1
unnamed: L7.P$1, U20.3
unnamed: C46.1, U20.1
unnamed: C48.1, R39.1, R40.2, R41.P$1, U21.4
unnamed: D7.A, R42.1
unnamed: L8.P$1, U23.3
unnamed: C53.1, U23.1
unnamed: C55.1, R45.1, R46.2, R47.P$1, U24.4
unnamed: D8.A, R48.1
unnamed: L9.P$1, U26.3
unnamed: C60.1, U26.1
unnamed: C62.1, R51.1, R52.2, R53.P$1, U27.4
unnamed: D9.A, R54.1
unnamed: L10.P$1, U29.3
unnamed: C67.1, U29.1
unnamed: C69.1, R57.1, R58.2, R59.P$1, U30.4
unnamed: D10.A, R60.1
unnamed: L11.P$1, U32.3
unnamed: C74.1, U32.1
unnamed: C76.1, R63.1, R64.2, R65.P$1, U33.4
unnamed: D11.A, R66.1
unnamed: L12.P$1, U35.3
unnamed: C81.1, U35.1
unnamed: C83.1, R69.1, R70.2, R71.P$1, U36.4
unnamed: D12.A, R72.1
unnamed: L13.P$1, U38.3
unnamed: C88.1, U38.1
unnamed: C90.1, R75.1, R76.2, R77.P$1, U39.4
unnamed: D13.A, R78.1
unnamed: L14.P$1, U41.3
unnamed: C95.1, U41.1
unnamed: C97.1, R81.1, R82.2, R83.P$1, U42.4
unnamed: D14.A, R84.1
unnamed: L15.P$1, U44.3
unnamed: C102.1, U44.1
unnamed: C104.1, R87.1, R88.2, R89.P$1, U45.4
unnamed: D15.A, R90.1
unnamed: L16.P$1, U47.3
unnamed: C109.1, U47.1
unnamed: C111.1, R93.1, R94.2, R95.P$1, U48.4
unnamed: D16.A, R96.1
unnamed: L17.P$1, U50.3
unnamed: C116.1, U50.1
unnamed: C118.1, R99.1, R100.2, R101.P$1, U51.4
unnamed: D17.A, R102.1
unnamed: L18.P$1, U53.3
unnamed: C123.1, U53.1
unnamed: C125.1, R105.1, R106.2, R107.P$1, U54.4
unnamed: D18.A, R108.1
unnamed: L19.P$1, U56.3
unnamed: C130.1, U56.1
unnamed: C132.1, R111.1, R112.2, R113.P$1, U57.4
unnamed: D19.A, R114.1
unnamed: L20.P$1, U59.3
unnamed: C137.1, U59.1
unnamed: C139.1, R117.1, R118.2, R119.P$1, U60.4
unnamed: D20.A, R120.1
unnamed: L21.P$1, U62.3
unnamed: C144.1, U62.1
unnamed: C146.1, R123.1, R124.2, R125.P$1, U63.4
unnamed: D21.A, R126.1
unnamed: L22.P$1, U65.3
unnamed: C151.1, U65.1
unnamed: C153.1, R129.1, R130.2, R131.P$1, U66.4
unnamed: D22.A, R132.1
unnamed: L23.P$1, U68.3
unnamed: C158.1, U68.1
unnamed: C160.1, R135.1, R136.2, R137.P$1, U69.4
unnamed: D23.A, R138.1
unnamed: L24.P$1, U71.3
unnamed: C165.1, U71.1
unnamed: C167.1, R141.1, R142.2, R143.P$1, U72.4
unnamed: D24.A, R144.1
unnamed: L25.P$1, U74.3
unnamed: C172.1, U74.1
unnamed: C174.1, R147.1, R148.2, R149.P$1, U75.4
unnamed: D25.A, R150.1
unnamed: L26.P$1, U77.3
unnamed: C179.1, U77.1
unnamed: C181.1, R153.1, R154.2, R155.P$1, U78.4
unnamed: D26.A, R156.1
unnamed: L27.P$1, U80.3
unnamed: C186.1, U80.1
unnamed: C188.1, R159.1, R160.2, R161.P$1, U81.4
unnamed: D27.A, R162.1
unnamed: L28.P$1, U83.3
unnamed: C193.1, U83.1
unnamed: C195.1, R165.1, R166.2, R167.P$1, U84.4
unnamed: D28.A, R168.1
unnamed: L29.P$1, U86.3
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
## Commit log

2018-05-23 updated VOUT programming
2018-05-23 Vout voltage from Vreg directly
2018-05-24 resizing board to 1x1 inch
2018-05-29 Adding top ground plane
2018-05-30 Updating design per review
2018-05-31 New labels
2018-05-31 Added text for warnings and jumper settings
2018-06-04 adding buzzard labels
2018-06-04 changing voltage output programming
2018-06-04 adding measurements
2018-06-05 Updated per QC review
2018-06-05 adding PROD ID prefix to 1.8M
2018-06-06 Updated pin labels to SparkX standards
2018-06-20 increased labels size
2018-06-22 Decreased board width, moved R1/R2 resistors
2018-06-25 Updating schematic notes to include resistor values for VOUT programming
2018-06-26 updated version number
2018-06-26 Updated version number on brd file
2018-06-26 Updates per Engineering Design Review
2018-06-26 Adding a lost fiducial
2018-06-27 updated MIC5205(ADJ) part
2018-07-11 v10 panel
2018-07-17 Updated gerbers with correct v-scores
2018-07-25 added v-scores note
2018-08-02 Adding project example code
2018-08-03 removing unused folders
2018-08-06 Update Path
    Moving to firmware folder.
2018-08-07 Update 5down32.ino
    Update code for a Arduino Pro Mini 3.3V/8MHz.
